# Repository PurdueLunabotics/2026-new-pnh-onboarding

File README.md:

Please put your files in a folder with your username on it

Eg, arepikov@purdue.edu -> arepikov

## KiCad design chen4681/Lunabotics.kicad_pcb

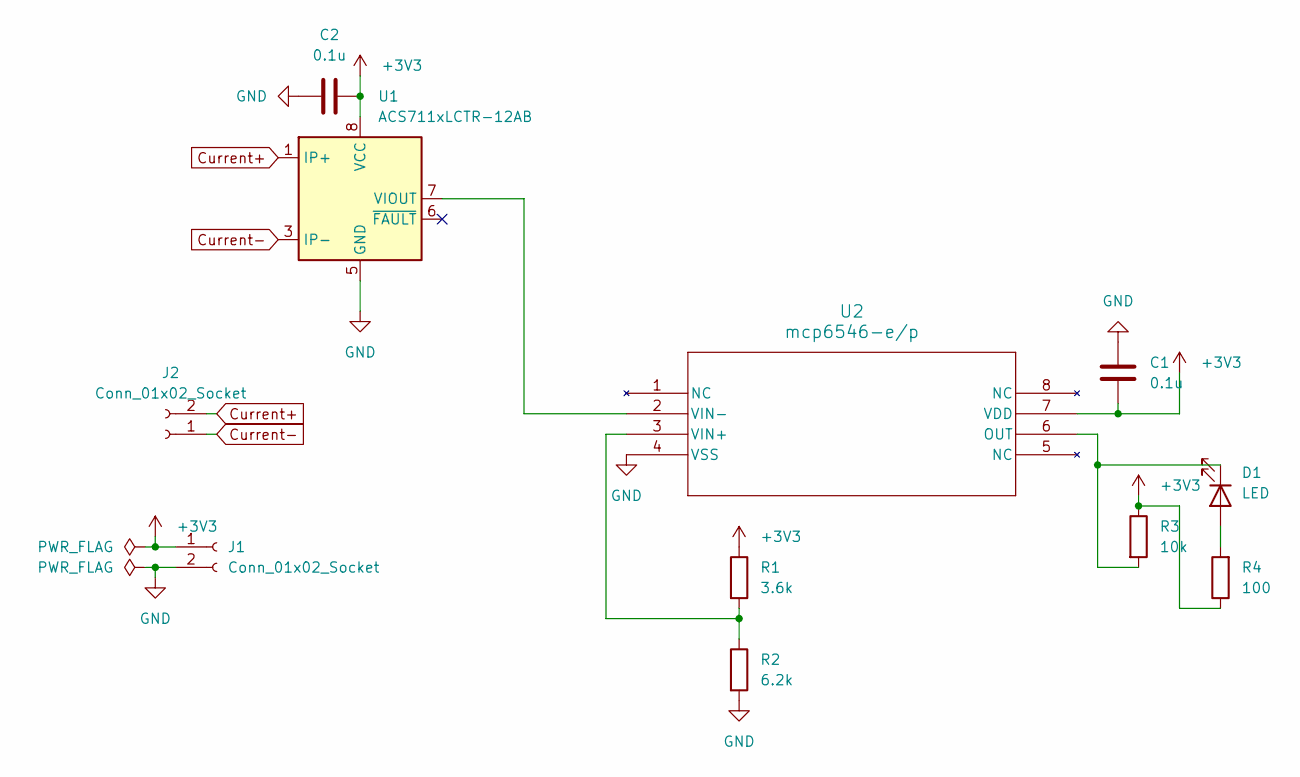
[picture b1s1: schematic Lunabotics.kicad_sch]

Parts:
C1, C2: 0.1u; C_0805_2012Metric
D1: LED; LED_D5.0mm
J1, J2: Conn_01x02_Socket; CUI_TB002-500-02BE
R1: 3.6k; R_Axial_DIN0411_L9.9mm_D3.6mm_P12.70mm_Horizontal
R2: 6.2k; R_Axial_DIN0411_L9.9mm_D3.6mm_P12.70mm_Horizontal
R3: 10k; R_Axial_DIN0411_L9.9mm_D3.6mm_P12.70mm_Horizontal
R4: 100; R_Axial_DIN0411_L9.9mm_D3.6mm_P12.70mm_Horizontal
U1: ACS711xLCTR-12AB; SOIC-8_3.9x4.9mm_P1.27mm
U2: mcp6546-e/p; DIP-8_W7.62mm

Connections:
+3V3: C1.2, C2.1, J1.1, R1.1, R3.1, R4.1, U1.8 (VCC), U2.7 (VDD)
Current+: J2.2, U1.1 (IP+), U1.2 (IP+)
Current-: J2.1, U1.3 (IP-), U1.4 (IP-)
GND: C1.1, C2.2, J1.2, R2.2, U1.5 (GND), U2.4 (VSS)
unnamed: D1.2 (A), R4.2
unnamed: D1.1 (K), R3.2, U2.6 (OUT)
unnamed: U1.7 (VIOUT), U2.2 (VIN-)
unnamed: R1.2, R2.1, U2.3 (VIN+)

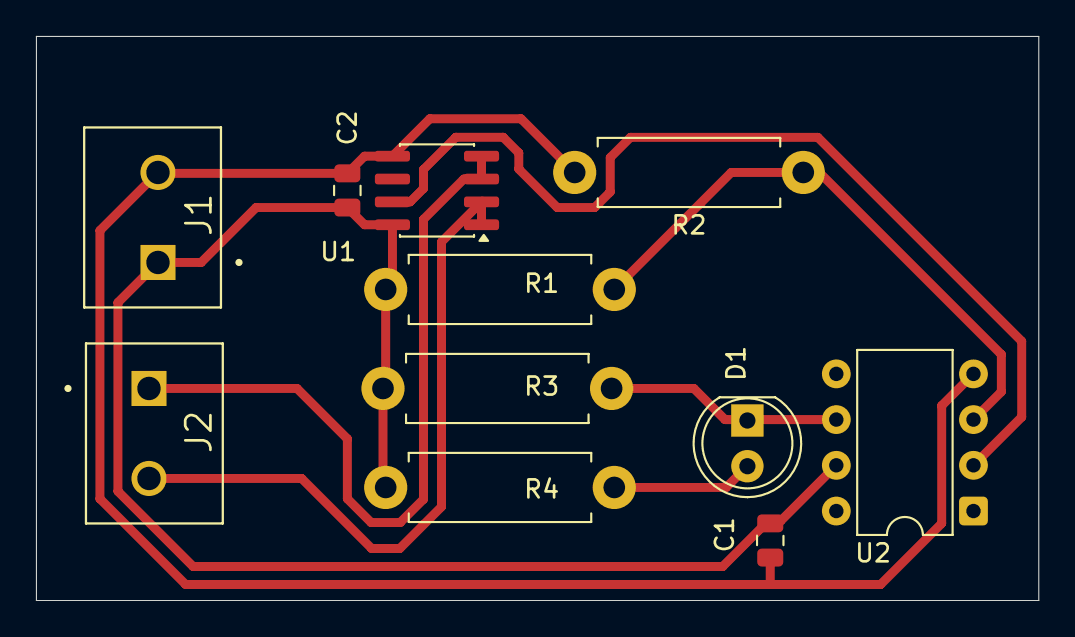
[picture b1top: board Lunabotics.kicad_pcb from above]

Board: 2 copper layers, 55.7 x 31.3 mm, 11 parts (0 on the bottom side), 8 nets.

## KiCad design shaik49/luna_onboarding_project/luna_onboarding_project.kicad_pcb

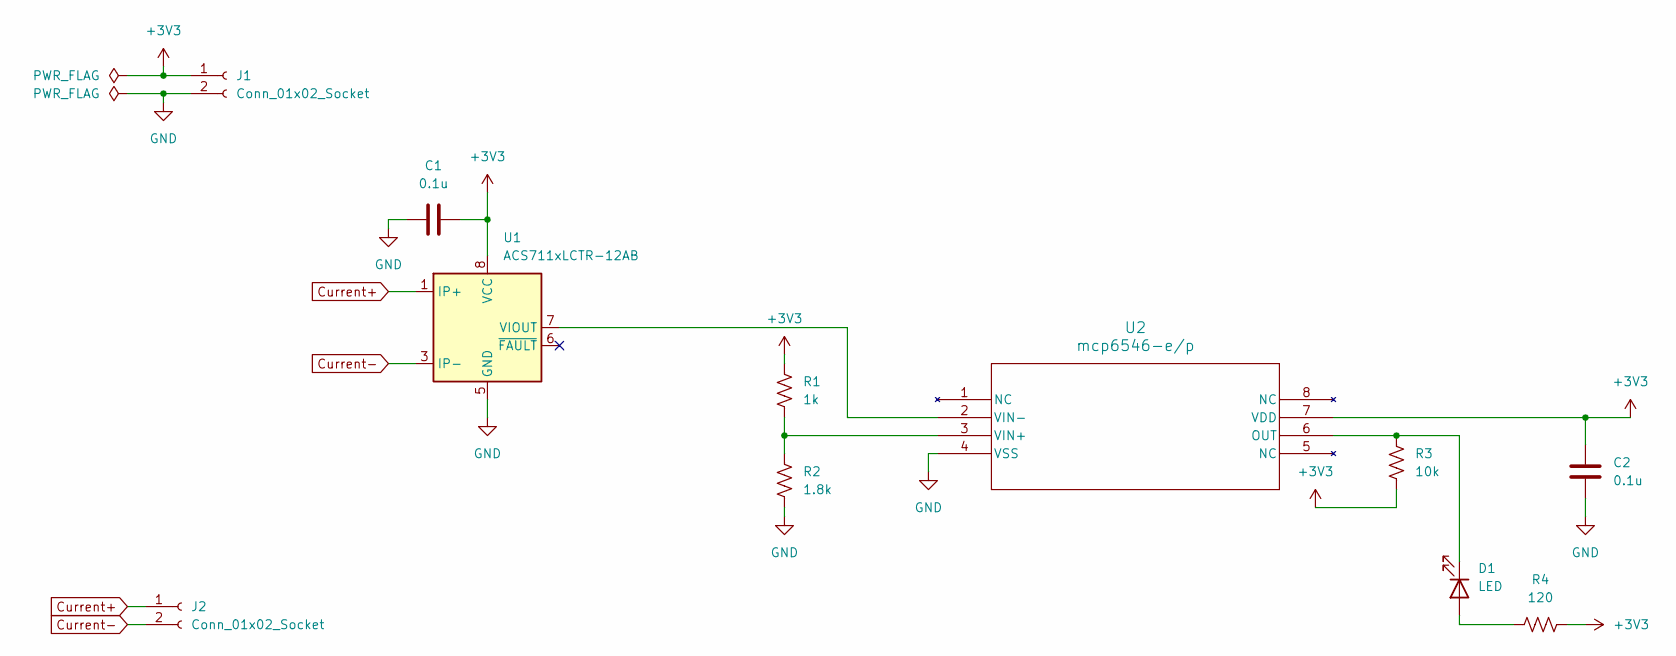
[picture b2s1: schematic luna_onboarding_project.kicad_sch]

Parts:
C1, C2: 0.1u; C_0805_2012Metric
D1: LED; LED_D5.0mm
J1, J2: Conn_01x02_Socket; CUI_TB002-500-02BE
R1: 1k; R_Axial_DIN0411_L9.9mm_D3.6mm_P12.70mm_Horizontal
R2: 1.8k; R_Axial_DIN0411_L9.9mm_D3.6mm_P12.70mm_Horizontal
R3: 10k; R_Axial_DIN0411_L9.9mm_D3.6mm_P12.70mm_Horizontal
R4: 120; R_Axial_DIN0411_L9.9mm_D3.6mm_P12.70mm_Horizontal
U1: ACS711xLCTR-12AB; SOIC-8_3.9x4.9mm_P1.27mm
U2: mcp6546-e/p; DIP-8_W7.62mm

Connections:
+3V3: C1.2, C2.1, J1.1, R1.1, R3.2, R4.2, U1.8 (VCC), U2.7 (VDD)
Current+: J2.1, U1.1 (IP+), U1.2 (IP+)
Current-: J2.2, U1.3 (IP-), U1.4 (IP-)
GND: C1.1, C2.2, J1.2, R2.2, U1.5 (GND), U2.4 (VSS)
unnamed: D1.2 (A), R4.1
unnamed: D1.1 (K), R3.1, U2.6 (OUT)
unnamed: U1.7 (VIOUT), U2.2 (VIN-)
unnamed: R1.2, R2.1, U2.3 (VIN+)

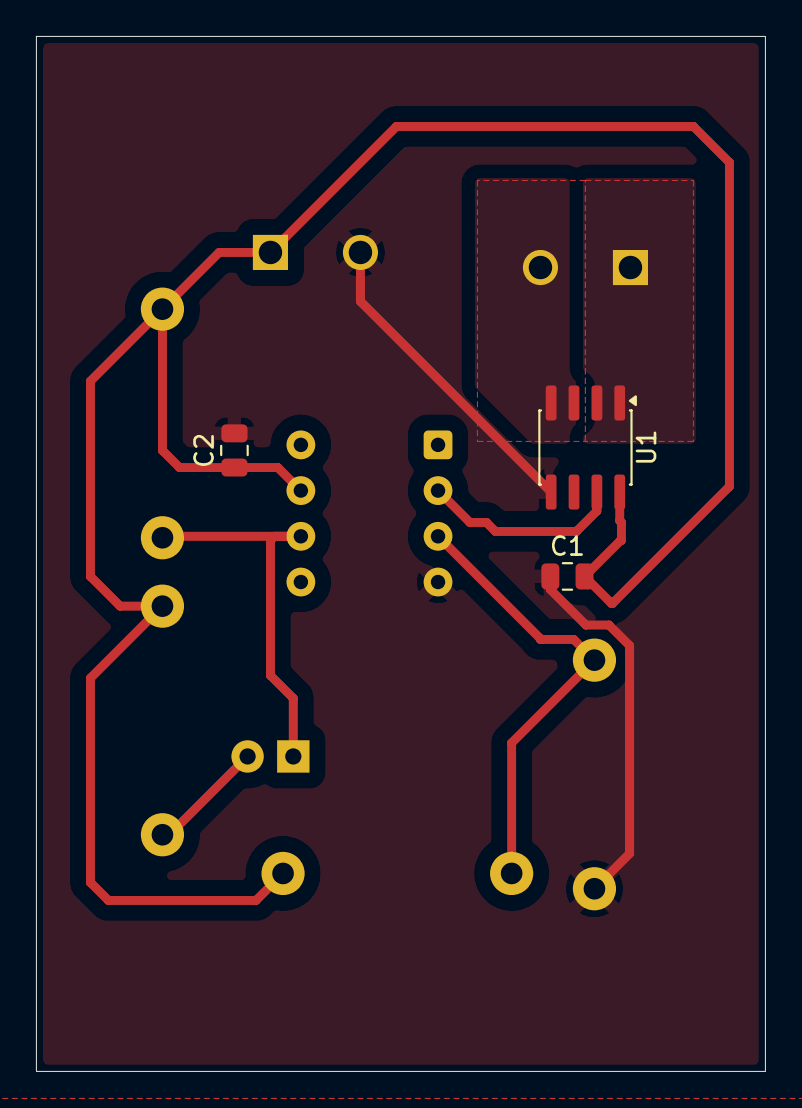
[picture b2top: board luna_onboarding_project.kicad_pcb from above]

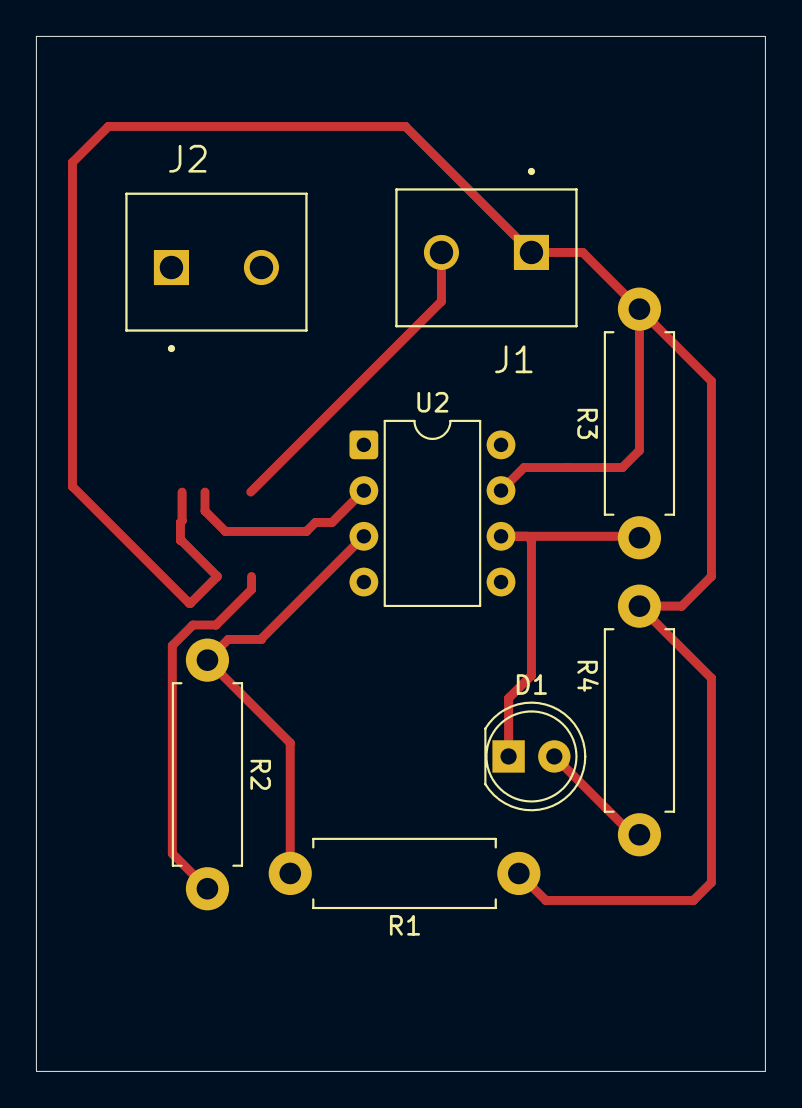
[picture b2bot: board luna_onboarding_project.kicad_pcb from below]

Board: 2 copper layers, 40.5 x 57.5 mm, 11 parts (8 on the bottom side), 8 nets.

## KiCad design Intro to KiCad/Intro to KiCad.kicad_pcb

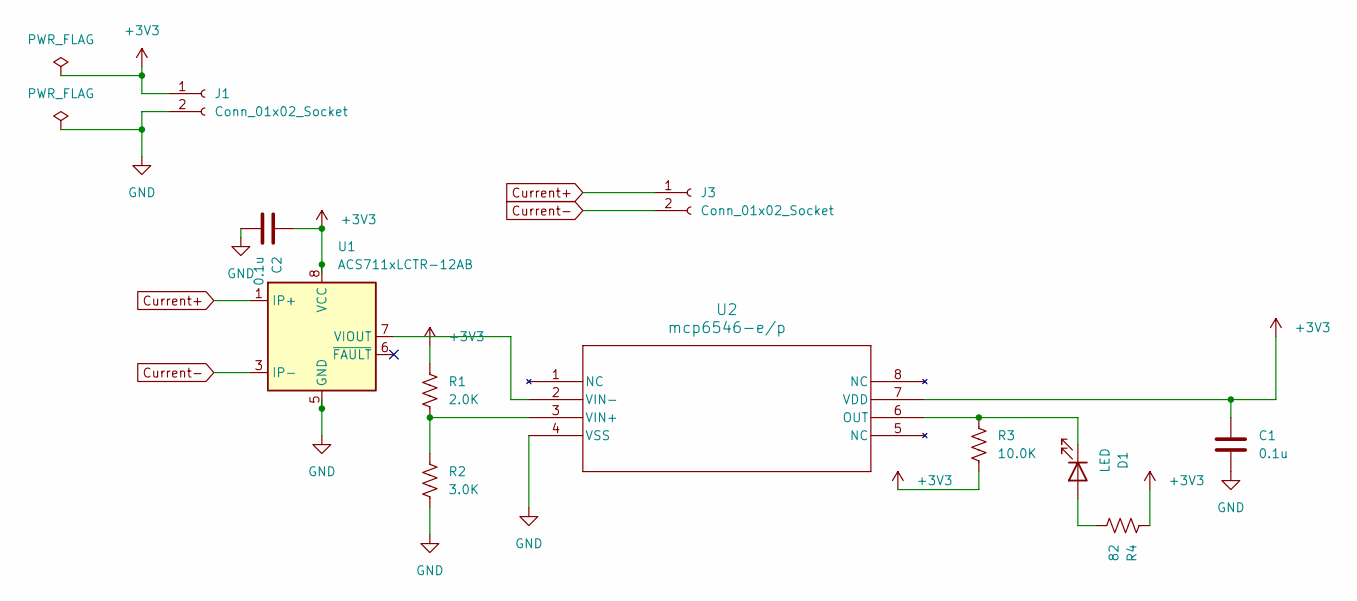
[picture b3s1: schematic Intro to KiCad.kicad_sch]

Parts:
C1, C2: 0.1u; C_0805_2012Metric
D1: LED; LED_D5.0mm
J1, J3: Conn_01x02_Socket; CUI_TB002-500-02BE
R1: 2.0K; R_Axial_DIN0411_L9.9mm_D3.6mm_P12.70mm_Horizontal
R2: 3.0K; R_Axial_DIN0411_L9.9mm_D3.6mm_P12.70mm_Horizontal
R3: 10.0K; R_Axial_DIN0411_L9.9mm_D3.6mm_P12.70mm_Horizontal
R4: 82; R_Axial_DIN0411_L9.9mm_D3.6mm_P12.70mm_Horizontal
U1: ACS711xLCTR-12AB; SOIC-8_3.9x4.9mm_P1.27mm
U2: mcp6546-e/p; DIP-8_W7.62mm

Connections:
+3V3: C1.1, C2.1, J1.1, R1.1, R3.2, R4.1, U1.8 (VCC), U2.7 (VDD)
Current+: J3.1, U1.1 (IP+), U1.2 (IP+)
Current-: J3.2, U1.3 (IP-), U1.4 (IP-)
GND: C1.2, C2.2, J1.2, R2.2, U1.5 (GND), U2.4 (VSS)
unnamed: D1.2 (A), R4.2
unnamed: D1.1 (K), R3.1, U2.6 (OUT)
unnamed: U1.7 (VIOUT), U2.2 (VIN-)
unnamed: R1.2, R2.1, U2.3 (VIN+)

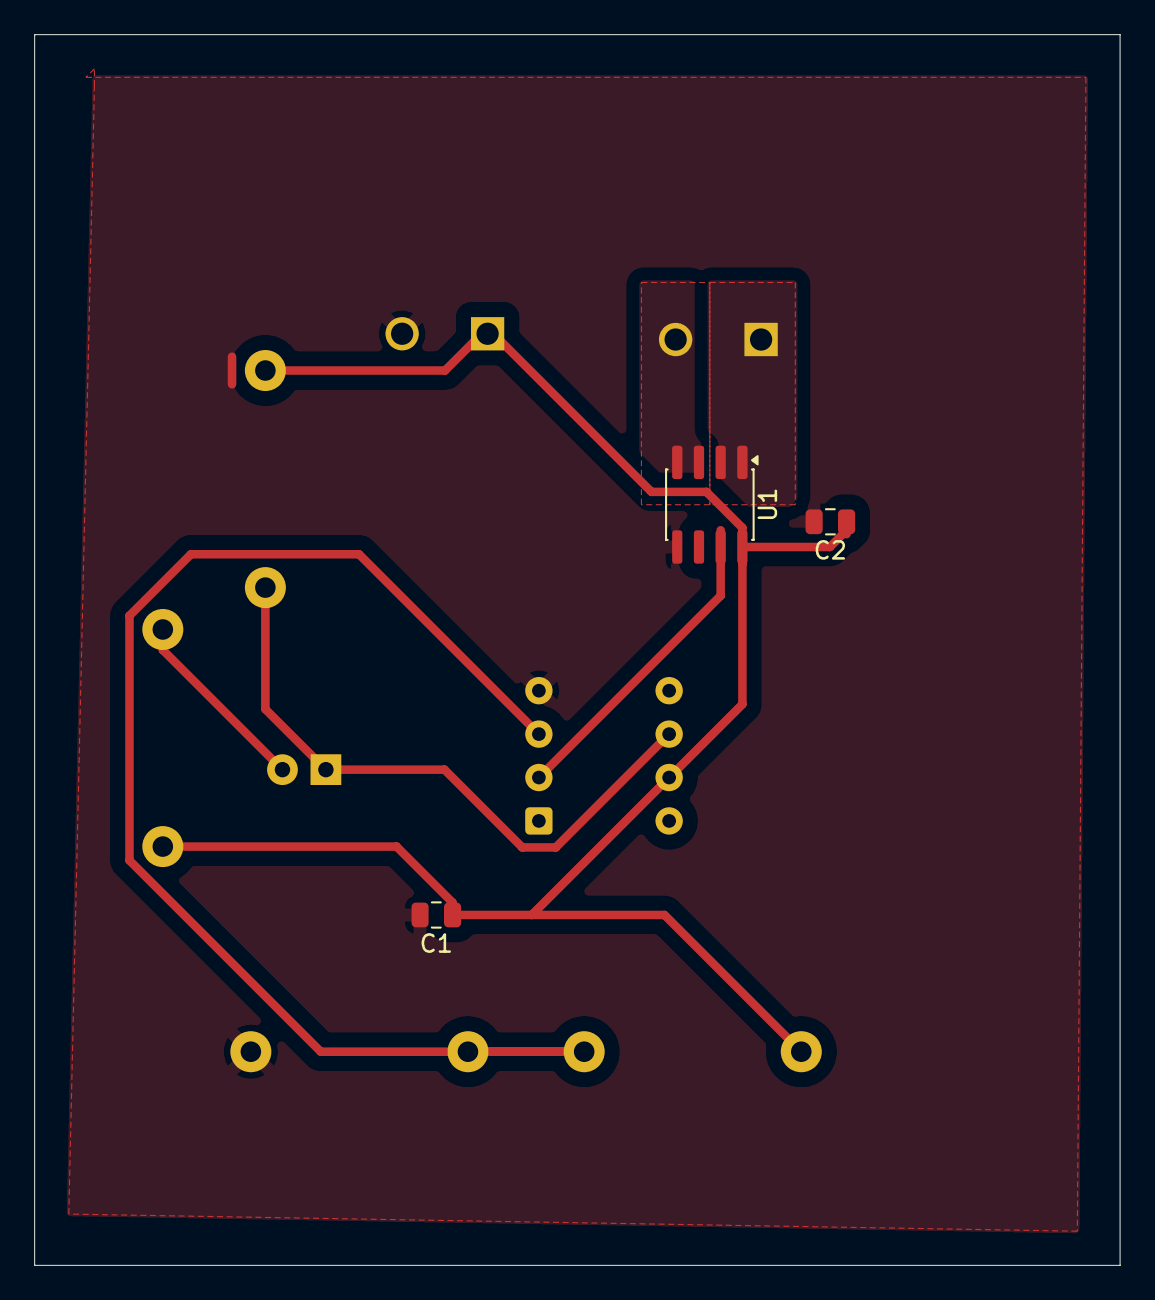
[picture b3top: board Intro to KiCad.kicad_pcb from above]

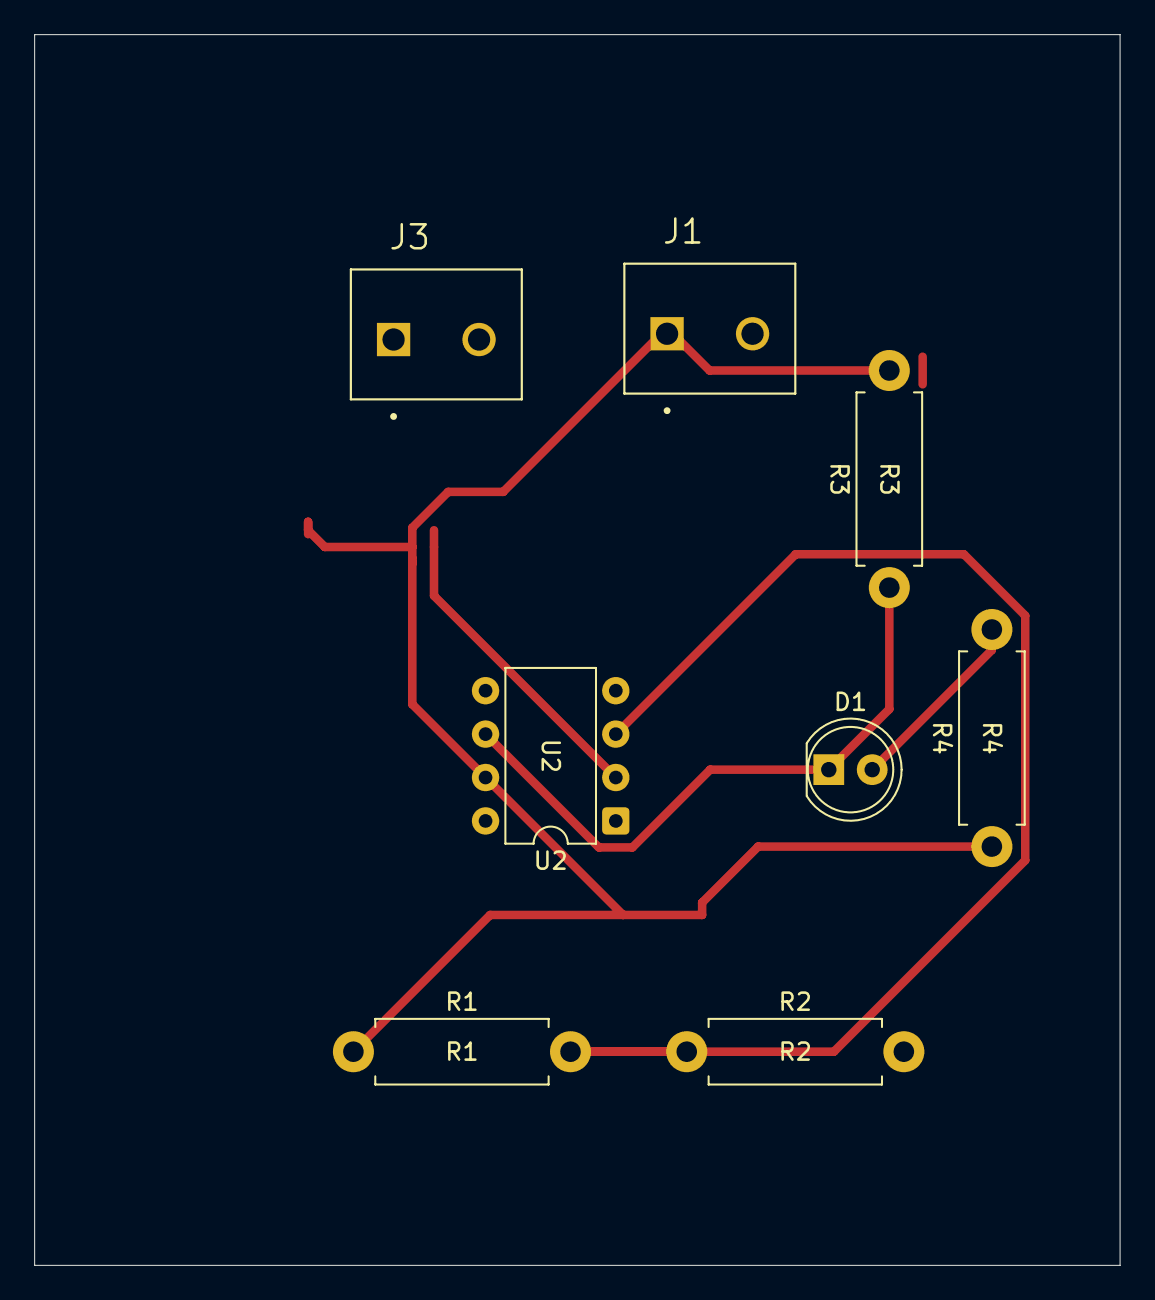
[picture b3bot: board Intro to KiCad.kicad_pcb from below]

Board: 2 copper layers, 63.5 x 72.0 mm, 11 parts (8 on the bottom side), 8 nets.

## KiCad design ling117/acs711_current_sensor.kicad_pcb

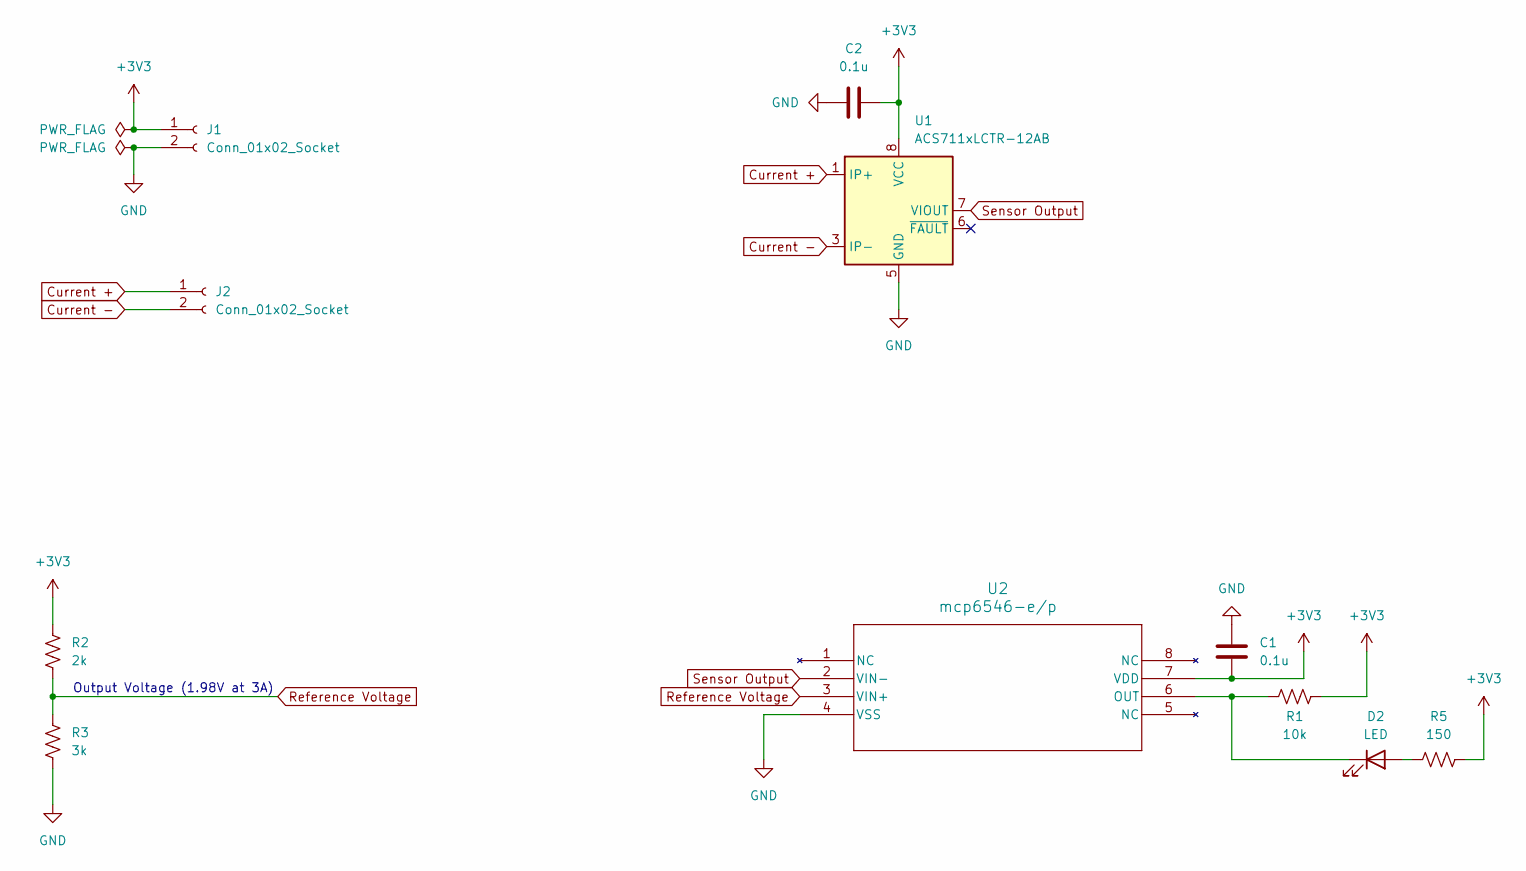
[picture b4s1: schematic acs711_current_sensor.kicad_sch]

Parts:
C1, C2: 0.1u; C_0805_2012Metric
D2: LED; LED_D5.0mm
J1, J2: Conn_01x02_Socket; CUI_TB002-500-02BE
R1: 10k; R_Axial_DIN0411_L9.9mm_D3.6mm_P12.70mm_Horizontal
R2: 2k; R_Axial_DIN0411_L9.9mm_D3.6mm_P12.70mm_Horizontal
R3: 3k; R_Axial_DIN0411_L9.9mm_D3.6mm_P12.70mm_Horizontal
R5: 150; R_Axial_DIN0411_L9.9mm_D3.6mm_P12.70mm_Horizontal
U1: ACS711xLCTR-12AB; SOIC-8_3.9x4.9mm_P1.27mm
U2: mcp6546-e/p; DIP-8_W7.62mm

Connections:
+3V3: C1.2, C2.2, J1.1, R1.2, R2.1, R5.2, U1.8 (VCC), U2.7 (VDD)
Current +: J2.1, U1.1 (IP+), U1.2 (IP+)
Current -: J2.2, U1.3 (IP-), U1.4 (IP-)
GND: C1.1, C2.1, J1.2, R3.2, U1.5 (GND), U2.4 (VSS)
unnamed: D2.2 (A), R5.1
unnamed: D2.1 (K), R1.1, U2.6 (OUT)
Reference Voltage: R2.2, R3.1, U2.3 (VIN+)
Sensor Output: U1.7 (VIOUT), U2.2 (VIN-)

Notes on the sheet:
Output Voltage (1.98V at 3A)

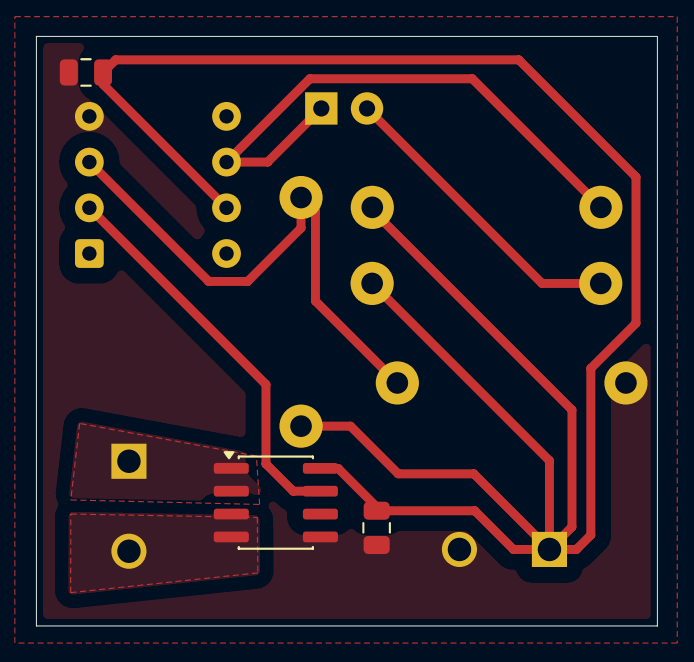
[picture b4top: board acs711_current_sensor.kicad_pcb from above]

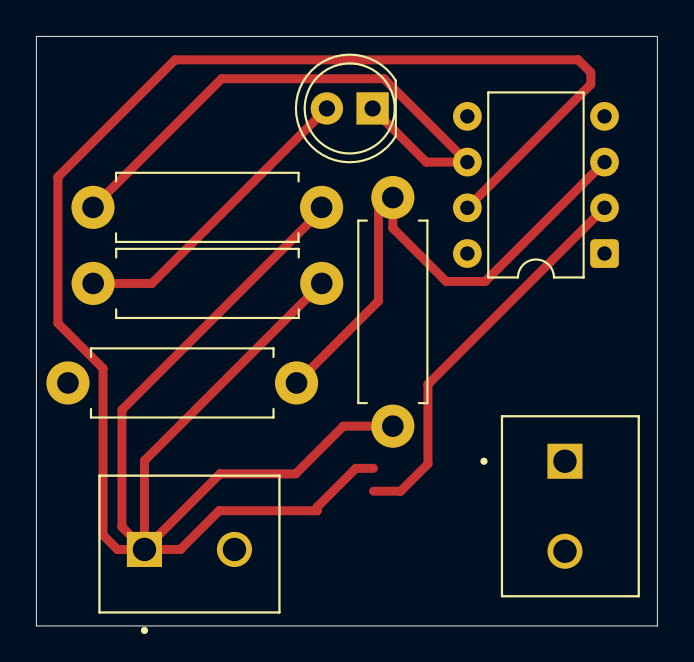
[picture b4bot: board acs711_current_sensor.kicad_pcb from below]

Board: 2 copper layers, 34.5 x 32.8 mm, 11 parts (8 on the bottom side), 8 nets.
